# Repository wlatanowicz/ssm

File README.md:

# ssm

Solar Scintillation Seeing Monitor based on `https://astropolis.pl/topic/59856-monitor-scyntylacji-słonecznej-ssm/`

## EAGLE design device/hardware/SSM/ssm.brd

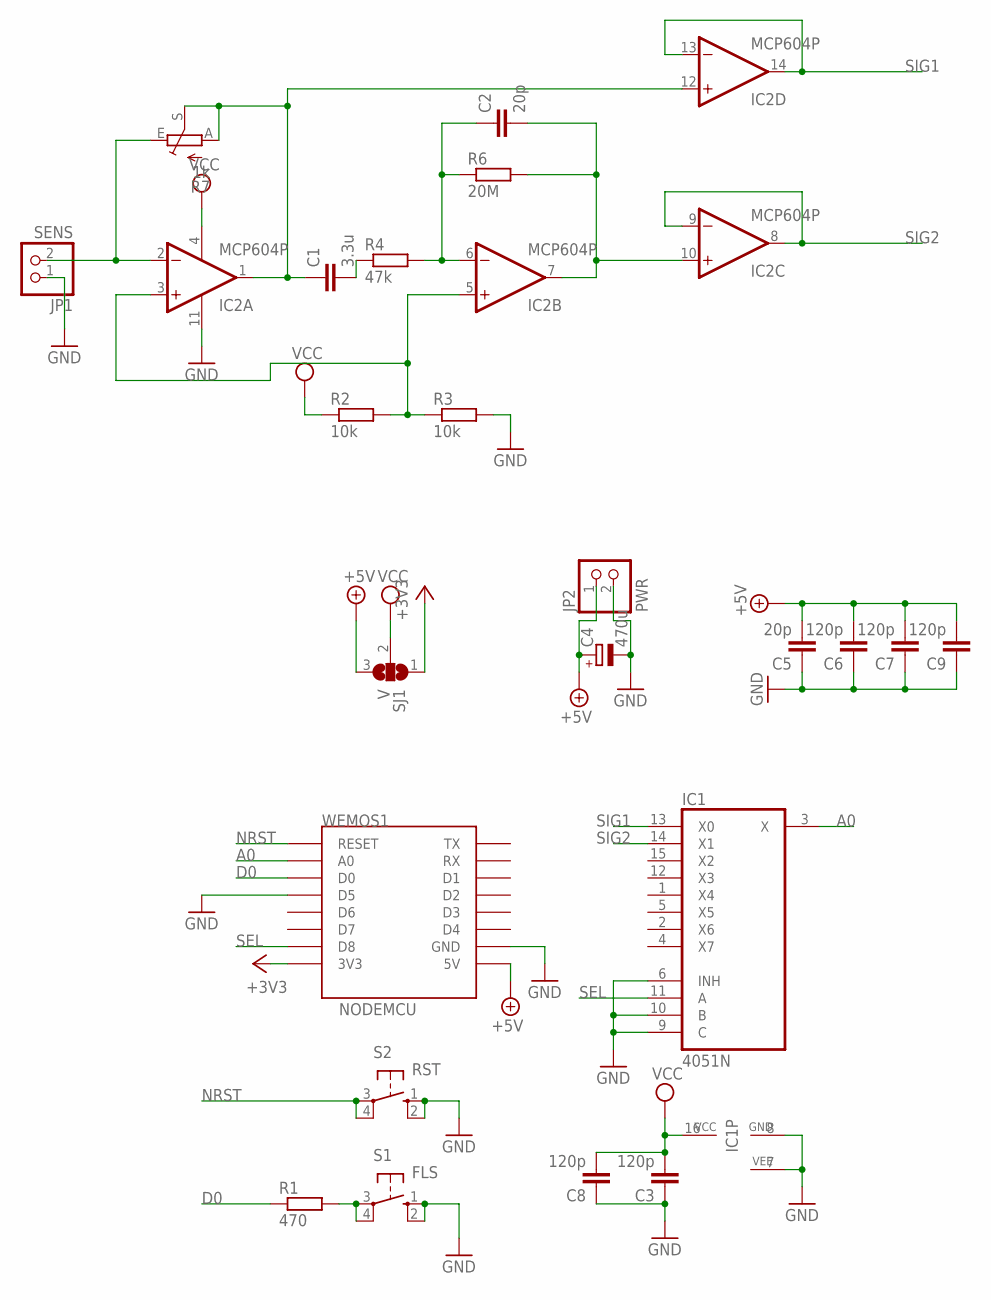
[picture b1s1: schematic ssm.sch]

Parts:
C1: 3.3u; C225-087X210
C2, C5: 20p; C025-024X044
C3, C6, C7, C8, C9: 120p; C025-024X044
C4: 470u; E2,5-5
IC1: 4051N; DIL16
IC2: MCP604P; DIL14
JP1: SENS; 1X02
JP2: PWR; 1X02
R1: 470; 0204/5
R2, R3: 10k; 0204/7
R4: 47k; 0204/7
R6: 20M; 0207/10
R7: 1k; B64Y
S1: FLS; B3F-10XX
S2: RST; B3F-10XX
SJ1: V; SJ_2
WEMOS1: NODEMCU; WEMOS-D1-MINI

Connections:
+3V3: SJ1.1, WEMOS1.3V3
+5V: C4.+, C5.2, C6.2, C7.2, C9.2, JP2.1, SJ1.3, WEMOS1.5V
A0: IC1.3 (X), WEMOS1.A0
D0: R1.1, WEMOS1.D0
GND: C3.1, C4.-, C5.1, C6.1, C7.1, C8.1, C9.1, IC1.6 (INH), IC1.7 (VEE), IC1.8 (GND), IC1.9 (C), IC1.10 (B), IC2.11 (V-), JP1.1, JP2.2, R3.2, S1.1 (S), S1.2 (S1), S2.1 (S), S2.2 (S1), WEMOS1.D5, WEMOS1.GND
unnamed: IC2.2 (-IN), JP1.2, R7.E
unnamed: R1.2, S1.3, S1.4 (P1)
unnamed: IC2.3 (+IN), IC2.5 (+IN), R2.2, R3.1
unnamed: C1.1, IC2.1 (OUT), IC2.12 (+IN), R7.A, R7.S
unnamed: C1.2, R4.1
unnamed: C2.1, IC2.6 (-IN), R4.2, R6.1
unnamed: C2.2, IC2.7 (OUT), IC2.10 (+IN), R6.2
NRST: S2.3, S2.4 (P1), WEMOS1.RESET
SEL: IC1.11 (A), WEMOS1.D8
SIG1: IC1.13 (X0), IC2.13 (-IN), IC2.14 (OUT)
SIG2: IC1.14 (X1), IC2.8 (OUT), IC2.9 (-IN)
VCC: C3.2, C8.2, IC1.16 (VCC), IC2.4 (V+), R2.1, SJ1.2

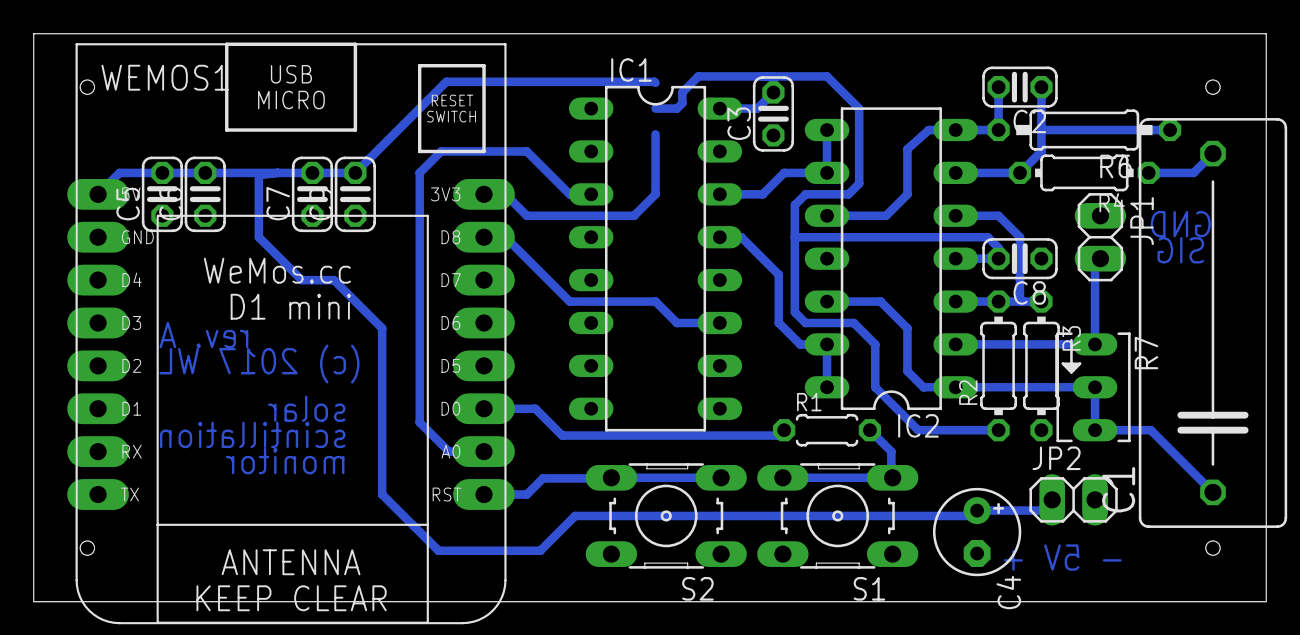
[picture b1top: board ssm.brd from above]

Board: 2 copper layers, 73.0 x 33.6 mm, 23 parts (1 on the bottom side), 17 nets.

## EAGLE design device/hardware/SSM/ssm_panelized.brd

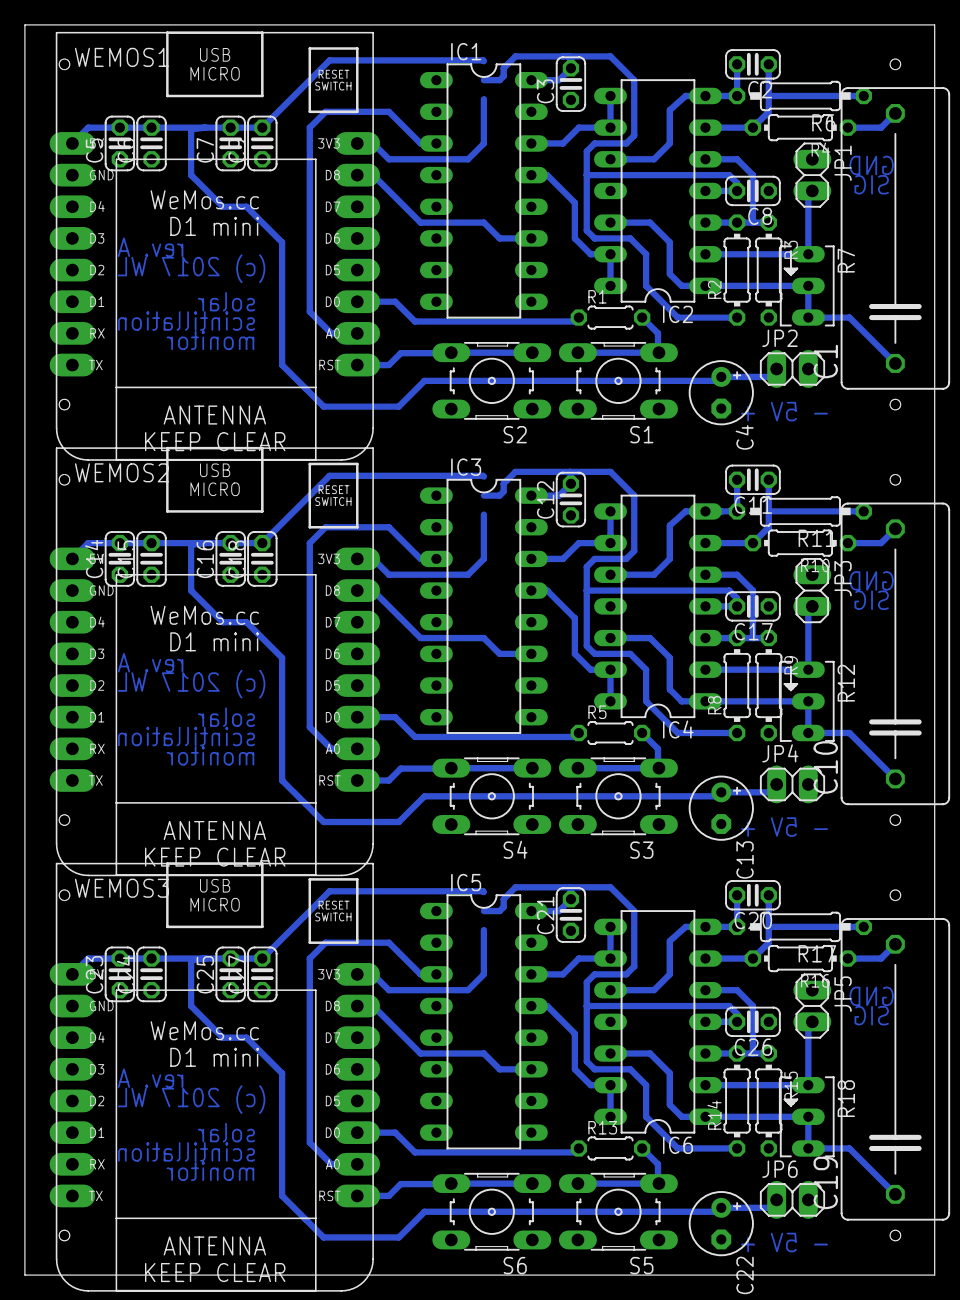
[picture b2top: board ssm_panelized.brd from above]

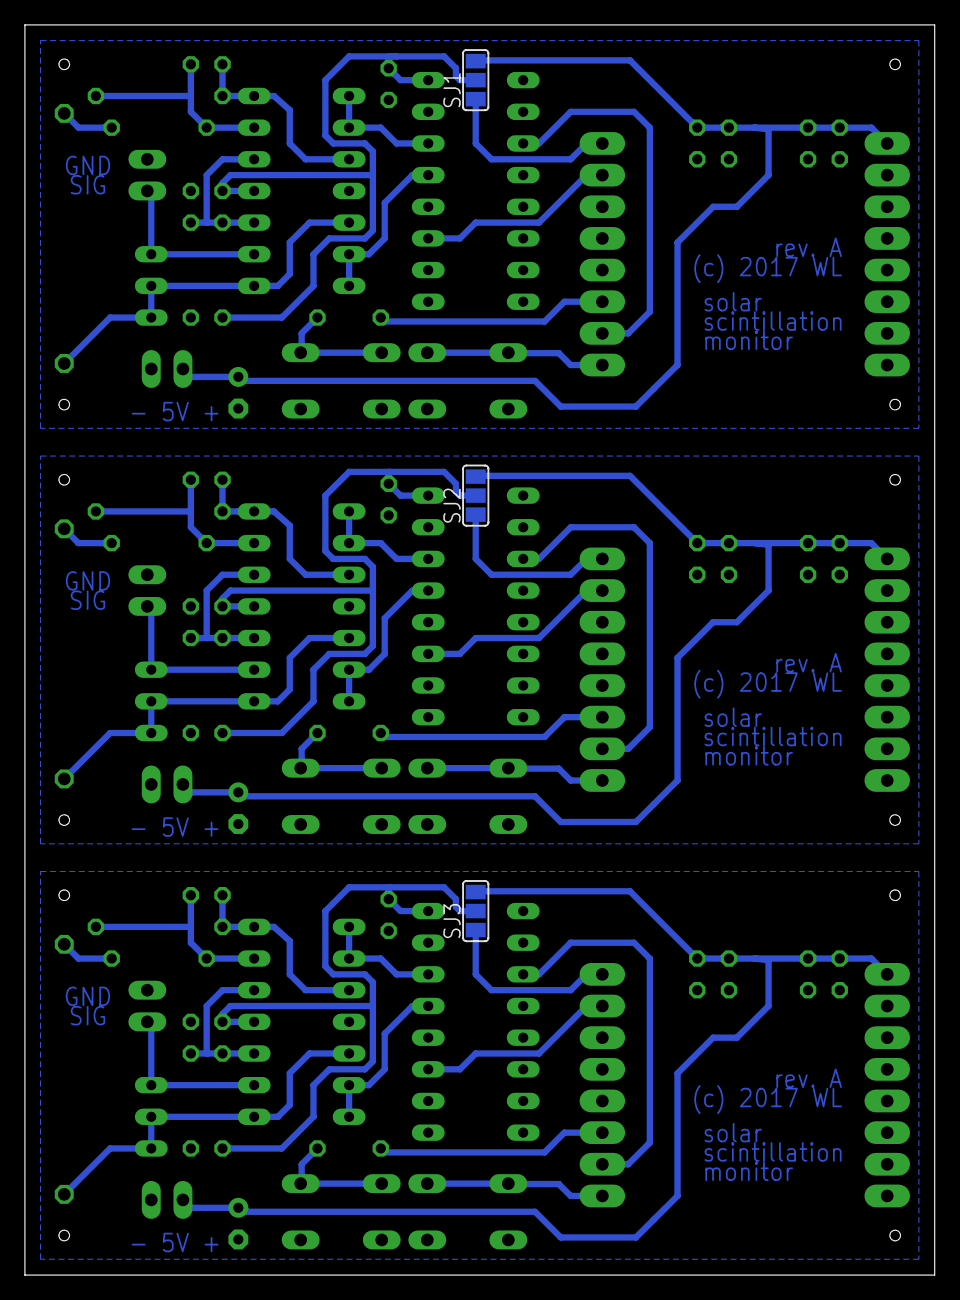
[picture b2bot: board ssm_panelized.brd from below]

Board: 2 copper layers, 73.0 x 100.3 mm, 69 parts (3 on the bottom side), 51 nets.

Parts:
C1, C10, C19: 3.3u; C225-087X210
C2, C5, C11, C14, C20, C23: 20p; C025-024X044
C3, C6, C7, C8, C9, C12, C15, C16, C17, C18, C21, C24, C25, C26, C27: 120p; C025-024X044
C4, C13, C22: 470u; E2,5-5
IC1, IC3, IC5: 4051N; DIL16
IC2, IC4, IC6: MCP604P; DIL14
JP1, JP3, JP5: SENS; 1X02
JP2, JP4, JP6: PWR; 1X02
R1, R5, R13: 470; 0204/5
R2, R3, R8, R9, R14, R15: 10k; 0204/7
R4, R10, R16: 47k; 0204/7
R6, R11, R17: 20M; 0207/10
R7, R12, R18: 1k; B64Y
S1, S3, S5: FLS; B3F-10XX
S2, S4, S6: RST; B3F-10XX
SJ1, SJ2, SJ3: V; SJ_2
WEMOS1, WEMOS2, WEMOS3: NODEMCU; WEMOS-D1-MINI

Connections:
+3V1: SJ2.1, WEMOS2.3V3
+3V2: SJ3.1, WEMOS3.3V3
+3V3: SJ1.1, WEMOS1.3V3
+5V: C4.+, C5.2, C6.2, C7.2, C9.2, JP2.1, SJ1.3, WEMOS1.5V
+5V1: C13.+, C14.2, C15.2, C16.2, C18.2, JP4.1, SJ2.3, WEMOS2.5V
+5V2: C22.+, C23.2, C24.2, C25.2, C27.2, JP6.1, SJ3.3, WEMOS3.5V
A0: IC1.3, WEMOS1.A0
A1: IC3.3, WEMOS2.A0
A2: IC5.3, WEMOS3.A0
D0: R1.1, WEMOS1.D0
D1: R5.1, WEMOS2.D0
D2: R13.1, WEMOS3.D0
GND: C3.1, C4.-, C5.1, C6.1, C7.1, C8.1, C9.1, IC1.6, IC1.7, IC1.8, IC1.9, IC1.10, IC2.11, JP1.1, JP2.2, R3.2, S1.1, S1.2, S2.1, S2.2, WEMOS1.D5, WEMOS1.GND
GND1: C12.1, C13.-, C14.1, C15.1, C16.1, C17.1, C18.1, IC3.6, IC3.7, IC3.8, IC3.9, IC3.10, IC4.11, JP3.1, JP4.2, R9.2, S3.1, S3.2, S4.1, S4.2, WEMOS2.D5, WEMOS2.GND
GND2: C21.1, C22.-, C23.1, C24.1, C25.1, C26.1, C27.1, IC5.6, IC5.7, IC5.8, IC5.9, IC5.10, IC6.11, JP5.1, JP6.2, R15.2, S5.1, S5.2, S6.1, S6.2, WEMOS3.D5, WEMOS3.GND
unnamed: R5.2, S3.3, S3.4
unnamed: IC2.2, JP1.2, R7.E
unnamed: R1.2, S1.3, S1.4
unnamed: IC2.3, IC2.5, R2.2, R3.1
unnamed: C1.1, IC2.1, IC2.12, R7.A, R7.S
unnamed: C1.2, R4.1
unnamed: C2.1, IC2.6, R4.2, R6.1
unnamed: C2.2, IC2.7, IC2.10, R6.2
unnamed: IC4.3, IC4.5, R8.2, R9.1
unnamed: IC4.2, JP3.2, R12.E
unnamed: C10.1, IC4.1, IC4.12, R12.A, R12.S
unnamed: C10.2, R10.1
unnamed: C11.1, IC4.6, R10.2, R11.1
unnamed: C11.2, IC4.7, IC4.10, R11.2
unnamed: R13.2, S5.3, S5.4
unnamed: IC6.3, IC6.5, R14.2, R15.1
unnamed: IC6.2, JP5.2, R18.E
unnamed: C19.1, IC6.1, IC6.12, R18.A, R18.S
unnamed: C19.2, R16.1
unnamed: C20.1, IC6.6, R16.2, R17.1
unnamed: C20.2, IC6.7, IC6.10, R17.2
NRST: S2.3, S2.4, WEMOS1.RESET
NRST1: S4.3, S4.4, WEMOS2.RESET
NRST2: S6.3, S6.4, WEMOS3.RESET
SEL: IC1.11, WEMOS1.D8
SEL1: IC3.11, WEMOS2.D8
SEL2: IC5.11, WEMOS3.D8
SIG1: IC1.13, IC2.13, IC2.14
SIG2: IC1.14, IC2.8, IC2.9
SIG3: IC3.13, IC4.13, IC4.14
SIG4: IC3.14, IC4.8, IC4.9
SIG5: IC5.13, IC6.13, IC6.14
SIG6: IC5.14, IC6.8, IC6.9
VCC: C3.2, C8.2, IC1.16, IC2.4, R2.1, SJ1.2
VCC1: C12.2, C17.2, IC3.16, IC4.4, R8.1, SJ2.2
VCC2: C21.2, C26.2, IC5.16, IC6.4, R14.1, SJ3.2

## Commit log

2017-08-26 pcb - initial version
2017-08-30 realign board for ordered parts
2017-08-30 gitignore
2017-08-30 cleanup custom cap lib
2017-09-01 panelized version
2017-09-01 move panels to 0,0
2017-09-02 fixes in panelized version
2017-09-12 work on data receiving server
2017-09-13 ws socket mock
2017-09-13 work on measurement storage
2017-09-14 prepare for bulk storing
2017-09-14 client mock ng bolierplate
2017-09-14 client mock ng
2017-09-15 proxy for kibana
2017-09-24 device folder cleanup, firmware
2017-09-24 wip: node mcu software
2017-10-24 timestamp conversion fix
2017-10-24 firmware
2017-10-24 receive only one value
2017-10-24 better logging
2017-10-25 mock fix, time from server
2017-10-26 led on transfer

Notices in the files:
device/hardware/SSM/ssm.brd:
(c) 2017 WL
